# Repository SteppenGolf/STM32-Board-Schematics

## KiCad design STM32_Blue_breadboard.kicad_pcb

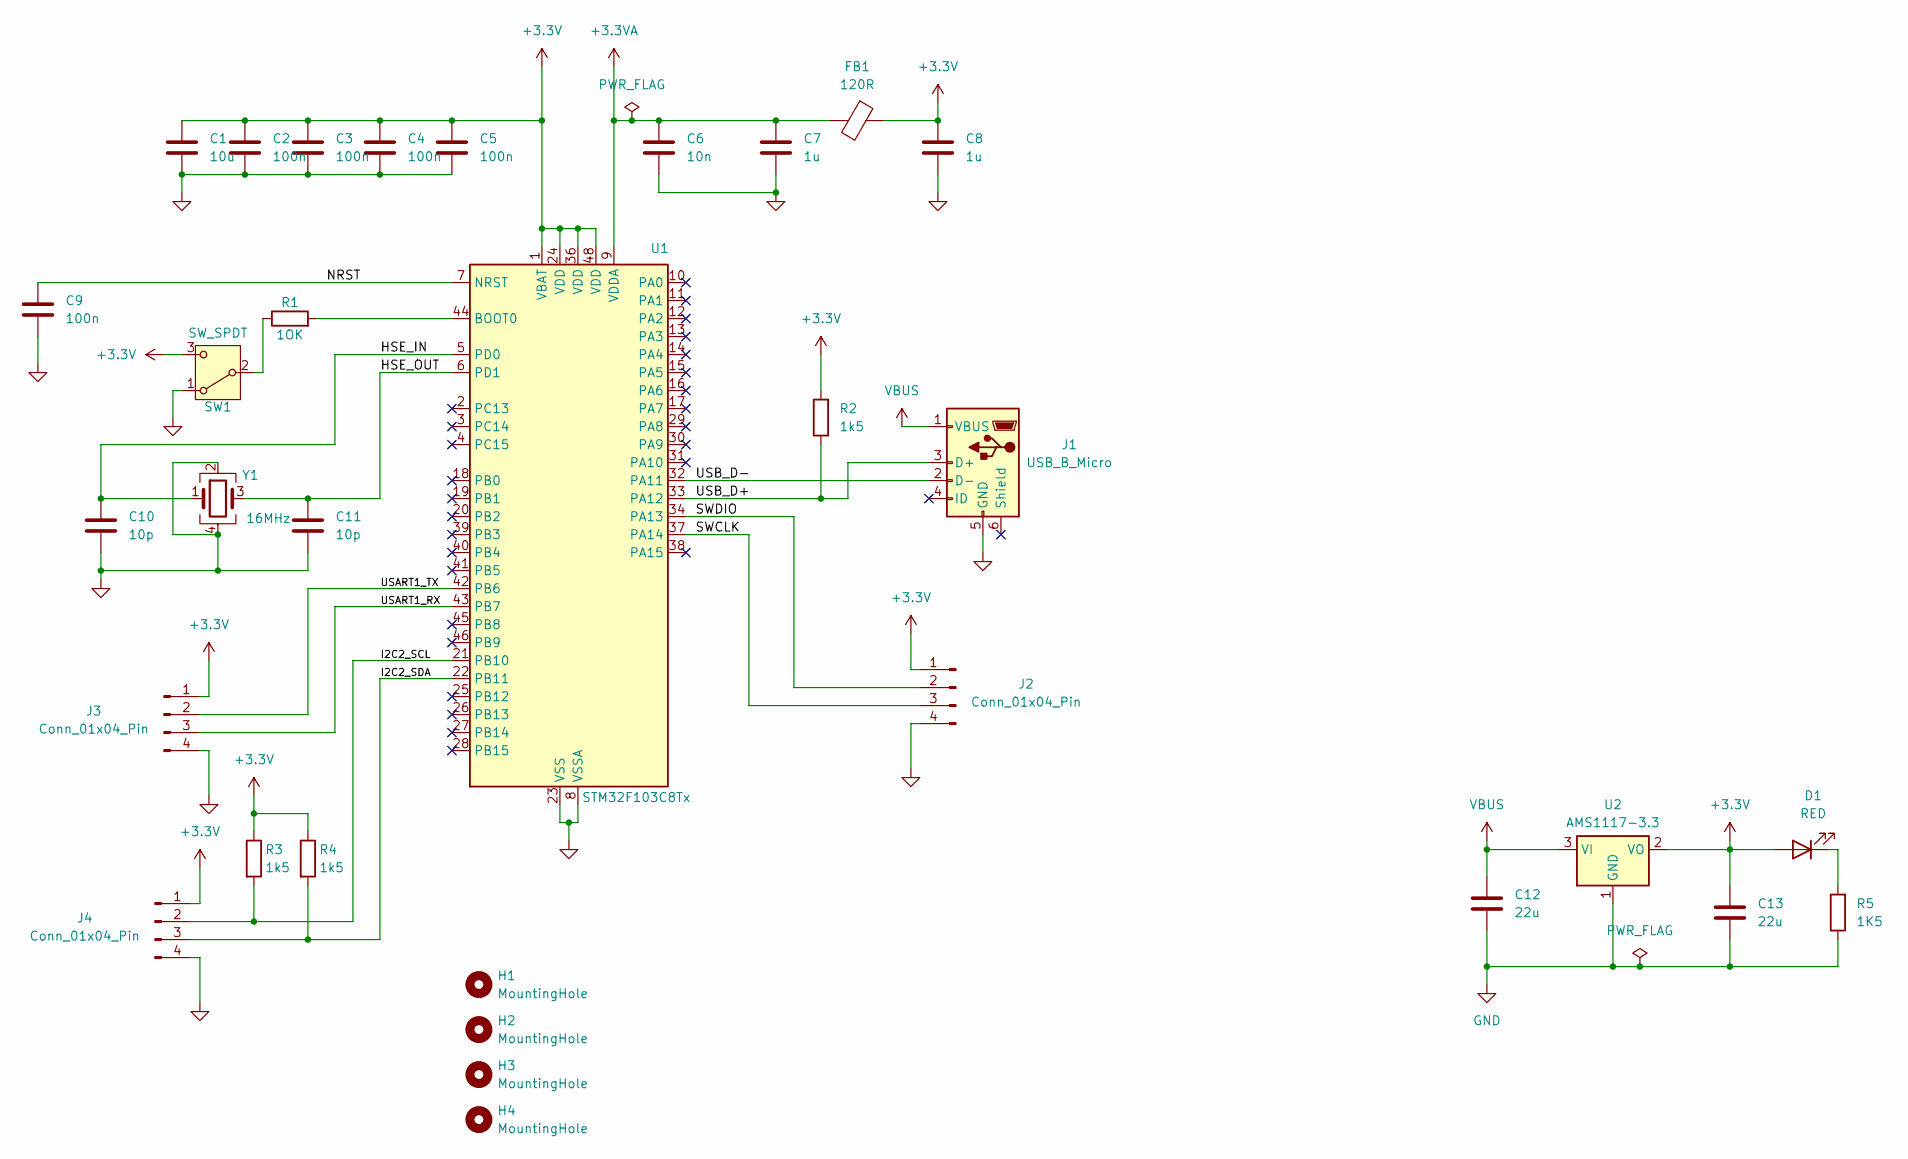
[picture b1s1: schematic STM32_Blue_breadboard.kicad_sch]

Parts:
C1: 10u; C_0603_1608Metric
C2, C3, C4, C5, C9: 100n; C_0402_1005Metric
C6: 10n; C_0402_1005Metric
C7, C8: 1u; C_0402_1005Metric
C10, C11: 10p; C_0402_1005Metric
C12, C13: 22u; C_0805_2012Metric
D1: RED; LED_0603_1608Metric
FB1: 120R; L_0603_1608Metric
H1, H2, H3, H4: MountingHole; MountingHole_2.2mm_M2
J1: USB_B_Micro; USB_Micro-B_Wuerth_614105150721_Vertical
J2, J3, J4: Conn_01x04_Pin; PinHeader_1x04_P2.54mm_Vertical
R1: 1OK; R_0402_1005Metric
R2, R3, R4: 1k5; R_0402_1005Metric
R5: 1K5; R_0402_1005Metric
SW1: SW_SPDT; Nidec_Copal_CAS-120A
U1: STM32F103C8Tx; LQFP-48_7x7mm_P0.5mm
U2: AMS1117-3.3; SOT-223-3_TabPin2
Y1: 16MHz; Crystal_SMD_3225-4Pin_3.2x2.5mm

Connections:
+3.3V: C1.1, C2.1, C3.1, C4.1, C5.1, C8.1, C13.1, D1.2 (A), FB1.1, J2.1, J3.1, J4.1, R2.2, R3.1, R4.1, SW1.3 (C), U1.1 (VBAT), U1.24 (VDD), U1.36 (VDD), U1.48 (VDD), U2.2 (VO)
+3.3VA: C6.1, C7.1, FB1.2, U1.9 (VDDA)
/HSE_IN: C10.1, U1.5 (PD0), Y1.1
/HSE_OUT: C11.1, U1.6 (PD1), Y1.3
/I2C2_SCL: J4.2, R3.2, U1.21 (PB10)
/I2C2_SDA: J4.3, R4.2, U1.22 (PB11)
/NRST: C9.1, U1.7 (NRST)
/SWCLK: J2.3, U1.37 (PA14)
/SWDIO: J2.2, U1.34 (PA13)
/USART1_RX: J3.3, U1.43 (PB7)
/USART1_TX: J3.2, U1.42 (PB6)
/USB_D+: J1.3 (D+), R2.1, U1.33 (PA12)
/USB_D-: J1.2 (D-), U1.32 (PA11)
<NO NET>: C1.2, C2.2, C3.2, C4.2, C5.2, C6.2, C7.2, C8.2, C9.2, C10.2, C11.2, J1.5 (GND), J2.4, J3.4, J4.4, SW1.1 (A), U1.8 (VSSA), U1.23 (VSS), U1.35 (VSS), U1.47 (VSS), Y1.2, Y1.4
GND: C12.2, C13.2, R5.1, U2.1 (GND)
unnamed: D1.1 (K), R5.2
unnamed: R1.1, SW1.2 (B)
unnamed: R1.2, U1.44 (BOOT0)
VBUS: C12.1, J1.1 (VBUS), U2.3 (VI)

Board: 2 copper layers, 32 parts (0 on the bottom side), 19 nets, no tracks yet.

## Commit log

2024-06-24 Initial commit
    Custom STM32 board with bluetooth.
